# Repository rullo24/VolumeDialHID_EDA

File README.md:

# Custom USB HID Volume Controller – KiCad Design
KiCad schematic and PCB layout for a USB HID volume controller based on the RP2040. Features rotary encoder for volume up, volume down, and play/pause, with USB-C and onboard voltage regulation.

## Features
- RP2040 microcontroller (QFN-56 package)
- USB-C with ESD protection and fuse
- Rotary encoder with pushbutton
- Status LEDs
- SWD and UART headers for debugging

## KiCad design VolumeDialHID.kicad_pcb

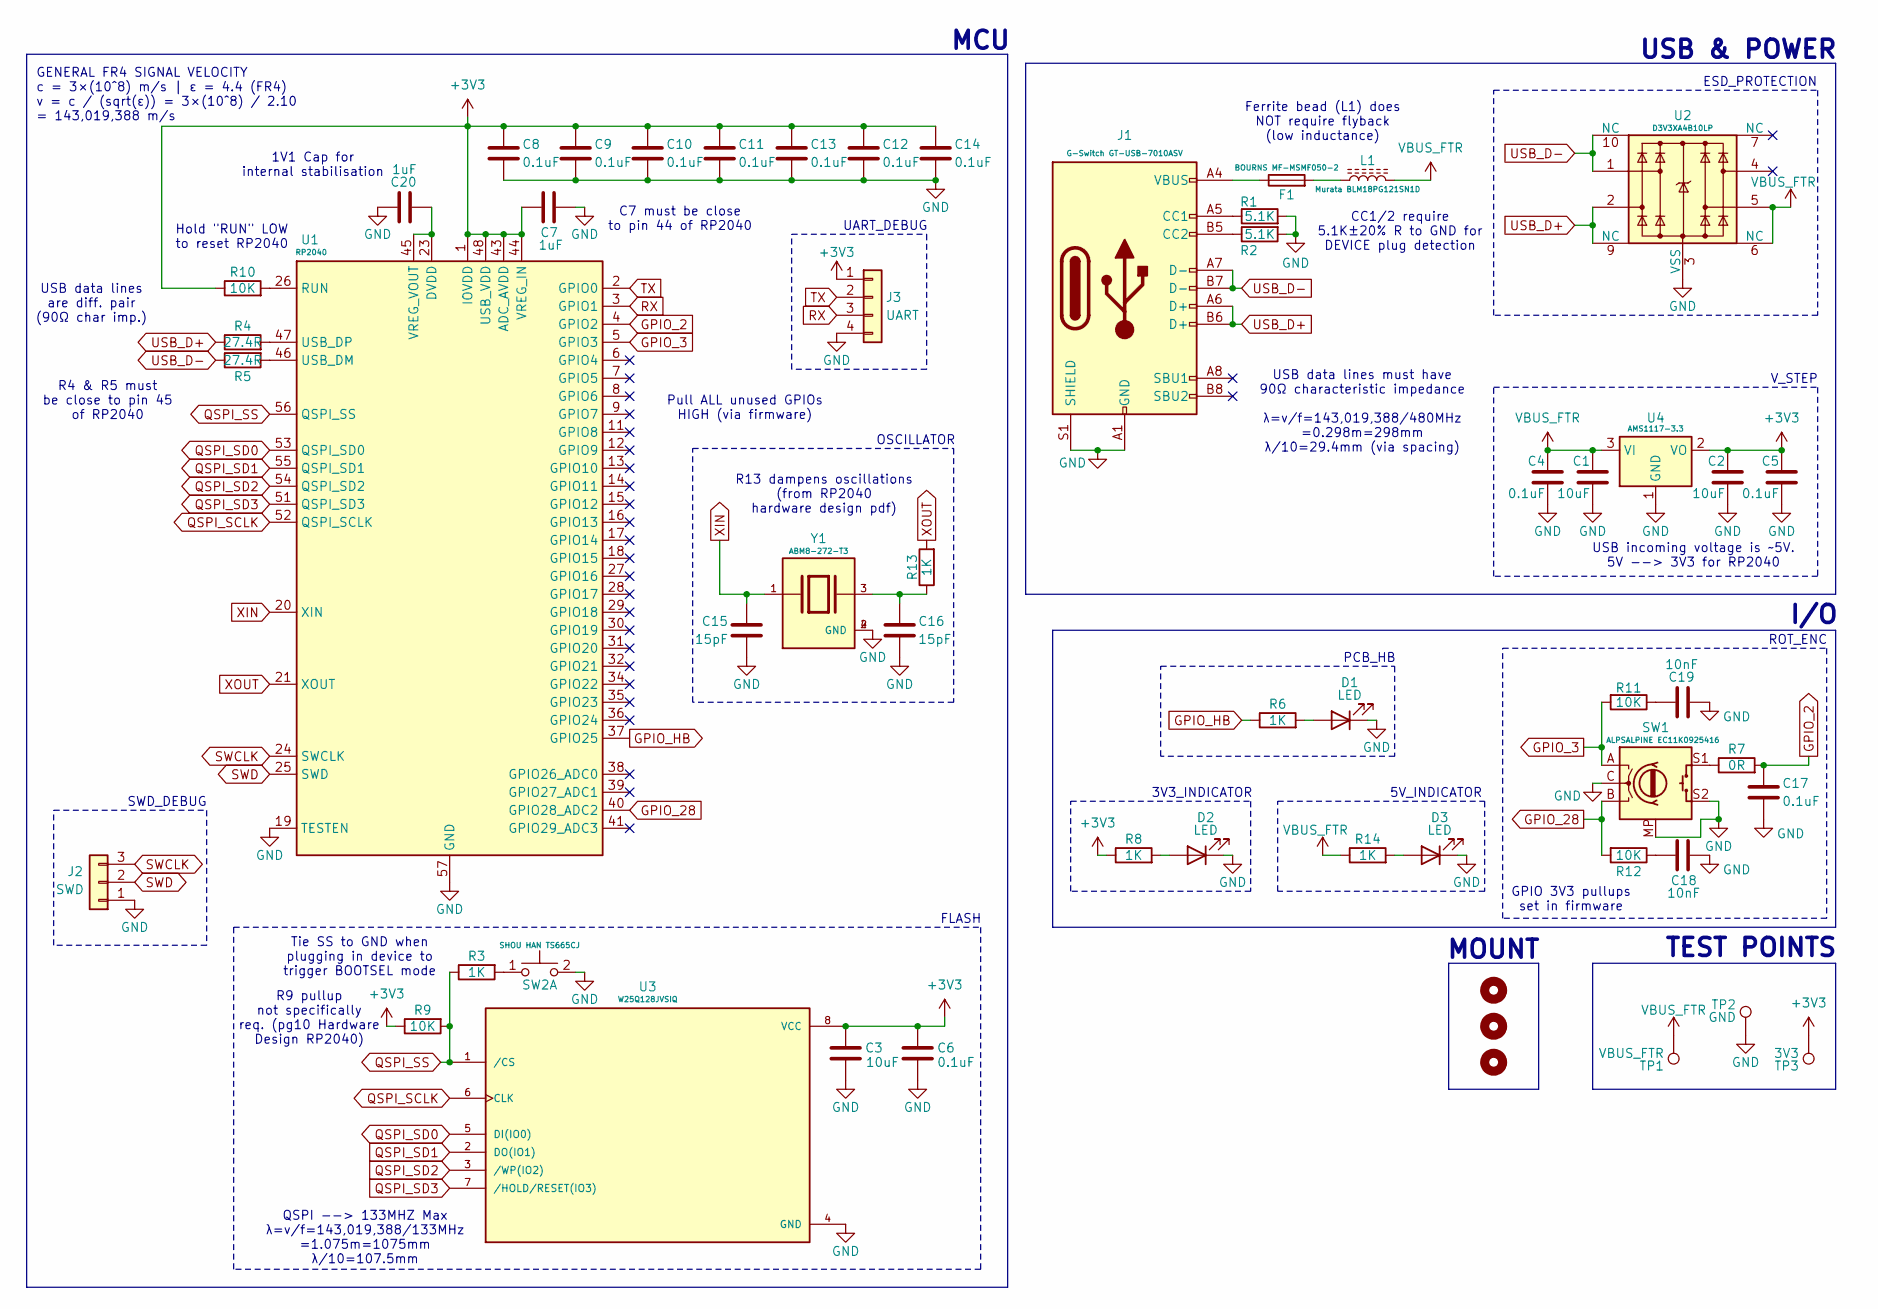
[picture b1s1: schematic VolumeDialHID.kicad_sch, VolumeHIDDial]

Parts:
C1, C2, C3: 10uF; C_0603_1608Metric
C4, C5, C6, C8, C9, C10, C11, C12, C13, C14, C17: 0.1uF; C_0603_1608Metric
C7, C20: 1uF; C_0603_1608Metric
C15, C16: 15pF; C_0603_1608Metric
C18, C19: 10nF; C_0603_1608Metric
D1, D2, D3: LED; LED_0603_1608Metric
F1: BOURNS MF-MSMF050-2; Fuse_1812_4532Metric
H1, H2, H3: MountingHole; MountingHole_3.2mm_M3_DIN965_Pad
J1: G-Switch GT-USB-7010ASV; USB_C_Receptacle_G-Switch_GT-USB-7010ASV
J2: SWD; PinHeader_1x03_P2.54mm_Vertical
J3: UART; PinHeader_1x04_P2.54mm_Vertical
L1: Murata BLM18PG121SN1D; Fuse_0603_1608Metric
R1, R2: 5.1K; R_0603_1608Metric
R3, R6, R8, R13, R14: 1K; R_0603_1608Metric
R4, R5: 27.4R; R_0603_1608Metric
R7: 0R; R_0603_1608Metric
R9, R10, R11, R12: 10K; R_0603_1608Metric
SW1: ALPSALPINE EC11K0925416; RotaryEncoder_Alps_EC11E-Switch_Vertical_H20mm
SW2: SHOU HAN TS665CJ; SW_PUSH_6mm
TP1: VBUS_FTR; TestPoint_Pad_1.0x1.0mm
TP2: GND; TestPoint_Pad_1.0x1.0mm
TP3: 3V3; TestPoint_Pad_1.0x1.0mm
U1: RP2040; QFN-56-1EP_7x7mm_P0.4mm_EP3.2x3.2mm
U2: D3V3XA4B10LP; Diodes_UDFN-10_1.0x2.5mm_P0.5mm
U3: W25Q128JVSIQ; SOIC127P790X216-8N; PARTREV I; DigiKey_Part_Number W25Q128JVSIQ-ND
U4: AMS1117-3.3; SOT-223
Y1: ABM8-272-T3; XTAL_ABM8-272-T3; PARTREV 07-29-20

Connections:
+3V3: C2.1, C3.2, C5.1, C6.2, C7.2, C8.1, C9.1, C10.1, C11.1, C12.1, C13.1, C14.1, J3.1, R8.1, R9.1, R10.1, TP3.1, U1.1 (IOVDD), U1.10 (IOVDD), U1.22 (IOVDD), U1.33 (IOVDD), U1.42 (IOVDD), U1.43 (ADC_AVDD), U1.44 (VREG_IN), U1.48 (USB_VDD), U1.49 (IOVDD), U3.8 (VCC), U4.2 (VO)
GND: C1.2, C2.2, C3.1, C4.2, C5.2, C6.1, C7.1, C8.2, C9.2, C10.2, C11.2, C12.2, C13.2, C14.2, C15.2, C16.2, C17.2, C18.1, C19.2, C20.1, D1.1 (K), D2.1 (K), D3.1 (K), J1.A1 (GND), J1.A12 (GND), J1.B1 (GND), J1.B12 (GND), J1.S1 (SHIELD), J2.1, J3.4, R1.2, R2.2, SW1.C, SW1.MP, SW1.S2, SW2.2 (D), TP2.1, U1.19 (TESTEN), U1.57 (GND), U2.3 (VSS), U2.8 (VSS), U3.4 (GND), U4.1 (GND), Y1.2 (GND), Y1.4 (GND)
GPIO_2: C17.1, R7.2, U1.4 (GPIO2)
GPIO_3: R11.2, SW1.A, U1.5 (GPIO3)
GPIO_28: R12.2, SW1.B, U1.40 (GPIO28_ADC2)
GPIO_HB: R6.1, U1.37 (GPIO25)
unnamed: C16.1, R13.1, Y1.3
unnamed: C18.2, R12.1
unnamed: C19.1, R11.1
unnamed: D1.2 (A), R6.2
unnamed: D2.2 (A), R8.2
unnamed: D3.2 (A), R14.2
unnamed: F1.1, J1.A4 (VBUS), J1.A9 (VBUS), J1.B4 (VBUS), J1.B9 (VBUS)
unnamed: F1.2, L1.1
unnamed: J1.A5 (CC1), R1.1
unnamed: J1.B5 (CC2), R2.1
unnamed: R7.1, SW1.S1
unnamed: R3.2, SW2.1 (C)
unnamed: R10.2, U1.26 (RUN)
unnamed: R5.2, U1.46 (USB_DM)
unnamed: R4.2, U1.47 (USB_DP)
unnamed: C20.2, U1.23 (DVDD), U1.45 (VREG_VOUT), U1.50 (DVDD)
QSPI_SCLK: U1.52 (QSPI_SCLK), U3.6 (CLK)
QSPI_SD0: U1.53 (QSPI_SD0), U3.5 (DI(IO0))
QSPI_SD1: U1.55 (QSPI_SD1), U3.2 (DO(IO1))
QSPI_SD2: U1.54 (QSPI_SD2), U3.3 (/WP(IO2))
QSPI_SD3: U1.51 (QSPI_SD3), U3.7 (/HOLD/RESET(IO3))
QSPI_SS: R3.1, R9.2, U1.56 (QSPI_SS), U3.1 (/CS)
RX: J3.3, U1.3 (GPIO1)
SWCLK: J2.3, U1.24 (SWCLK)
SWD: J2.2, U1.25 (SWD)
TX: J3.2, U1.2 (GPIO0)
USB_D+: J1.A6 (D+), J1.B6 (D+), R4.1, U2.2, U2.9 (NC)
USB_D-: J1.A7 (D-), J1.B7 (D-), R5.1, U2.1, U2.10 (NC)
VBUS_FTR: C1.1, C4.1, L1.2, R14.1, TP1.1, U2.5, U2.6 (NC), U4.3 (VI)
XIN: C15.1, U1.20 (XIN), Y1.1
XOUT: R13.2, U1.21 (XOUT)

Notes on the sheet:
V_STEP
USB & POWER
5V_INDICATOR
USB data lines are diff. pair (90Ω char imp.)
1V1 Cap for internal stabilisation
ROT_ENC
GPIO 3V3 pullups set in firmware
C7 must be close to pin 44 of RP2040
UART_DEBUG
SWD_DEBUG
GENERAL FR4 SIGNAL VELOCITY c = 3×(10^8) m/s | ε = 4.4 (FR4) v = c / (sqrt(ε)) = 3×(10^8) / 2.10 = 143,019,388 m/s
R4 & R5 must be close to pin 45 of RP2040
Pull ALL unused GPIOs HIGH (via firmware)
OSCILLATOR
PCB_HB
FLASH
USB incoming voltage is ~5V. 5V --> 3V3 for RP2040
Tie SS to GND when plugging in device to trigger BOOTSEL mode
USB data lines must have 90Ω characteristic impedance λ=v/f=143,019,388/480MHz =0.298m=298mm λ/10=29.4mm (via spacing)
I/O
R13 dampens oscillations (from RP2040 hardware design pdf)
CC1/2 require 5.1K±20% R to GND for DEVICE plug detection
ESD_PROTECTION
MCU
3V3_INDICATOR
R9 pullup not specifically req. (pg10 Hardware Design RP2040)
MOUNT
Ferrite bead (L1) does NOT require flyback (low inductance)
TEST POINTS
Hold "RUN" LOW to reset RP2040
QSPI --> 133MHZ Max λ=v/f=143,019,388/133MHz =1.075m=1075mm λ/10=107.5mm

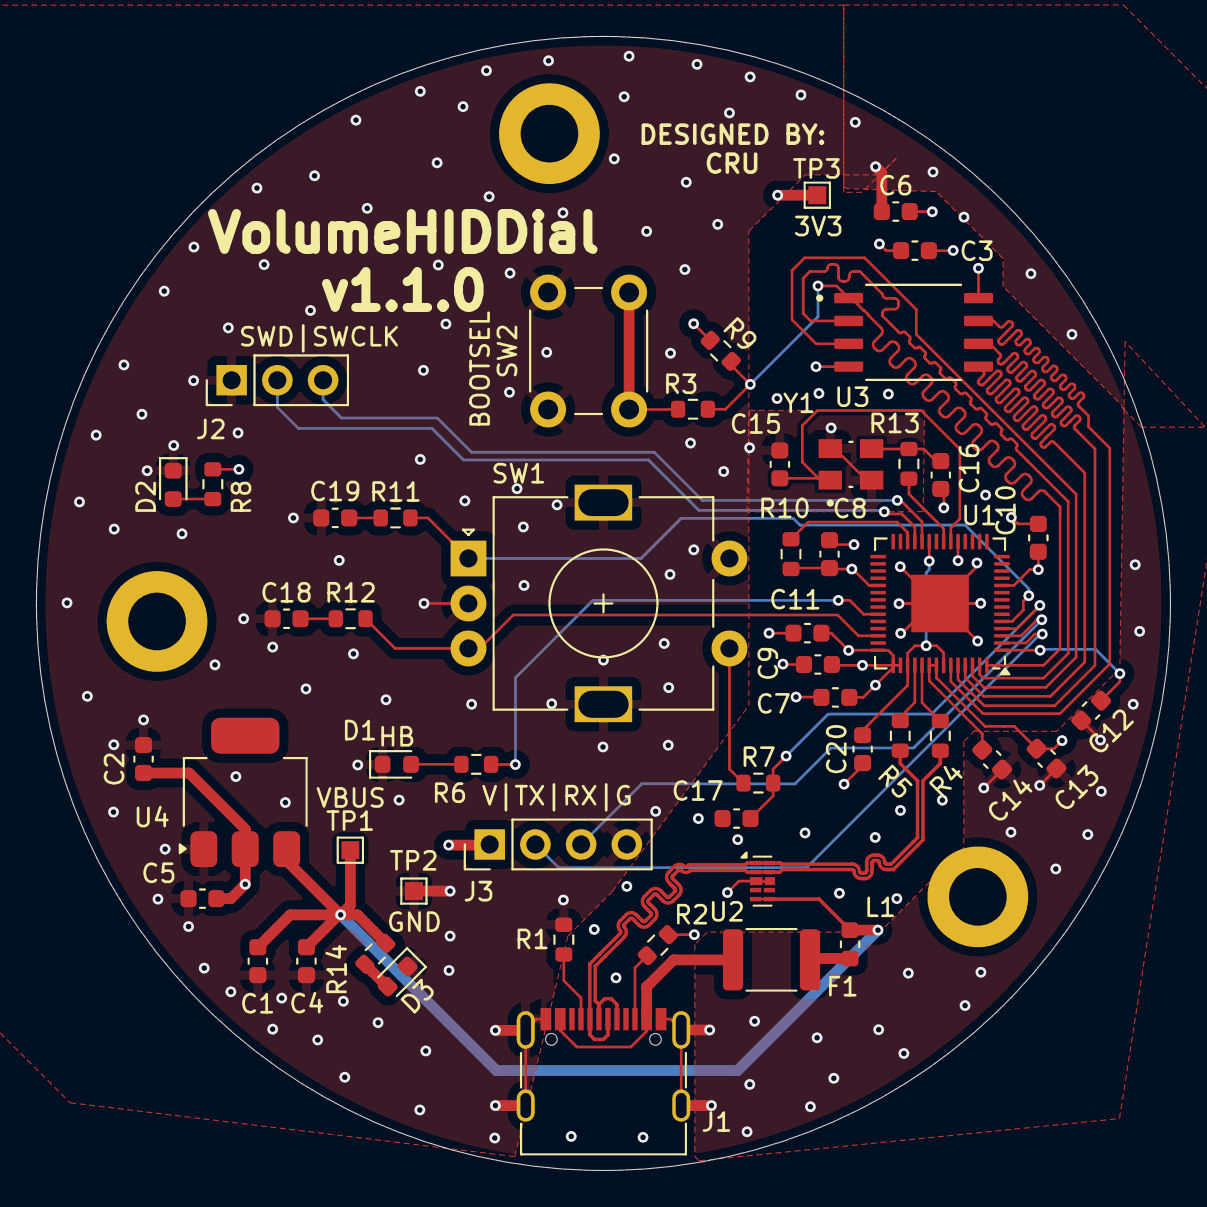
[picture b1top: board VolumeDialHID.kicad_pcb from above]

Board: 4 copper layers, 63.0 x 63.0 mm, 55 parts (0 on the bottom side), 37 nets.

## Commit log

2025-07-21 v1.1.0
